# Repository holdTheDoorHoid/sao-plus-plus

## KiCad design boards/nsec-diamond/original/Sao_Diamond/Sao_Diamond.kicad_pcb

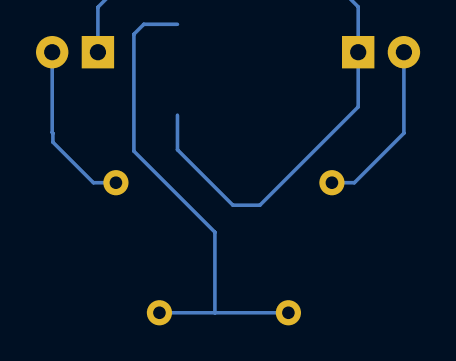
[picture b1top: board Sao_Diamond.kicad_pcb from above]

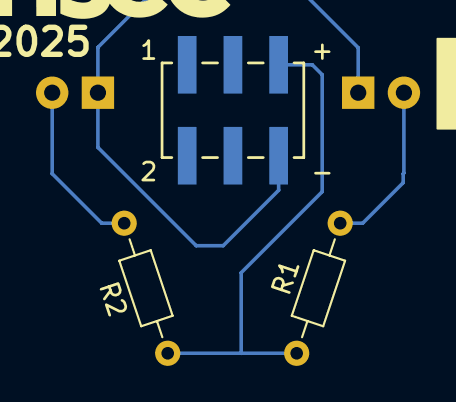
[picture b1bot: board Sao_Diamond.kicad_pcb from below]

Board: 2 copper layers, 5 parts (3 on the bottom side), 4 nets.

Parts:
D1, D2: LED; LED_D3.0mm
J1: SAO Connector SMD
R1, R2: 330; R_Axial_DIN0204_L3.6mm_D1.6mm_P7.62mm_Horizontal

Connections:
+3.3V: J1.5 (3V3), R1.1, R2.1
GND: D1.1 (K), D2.1 (K), J1.6 (GND)
unnamed: D1.2 (A), R1.2
unnamed: D2.2 (A), R2.2

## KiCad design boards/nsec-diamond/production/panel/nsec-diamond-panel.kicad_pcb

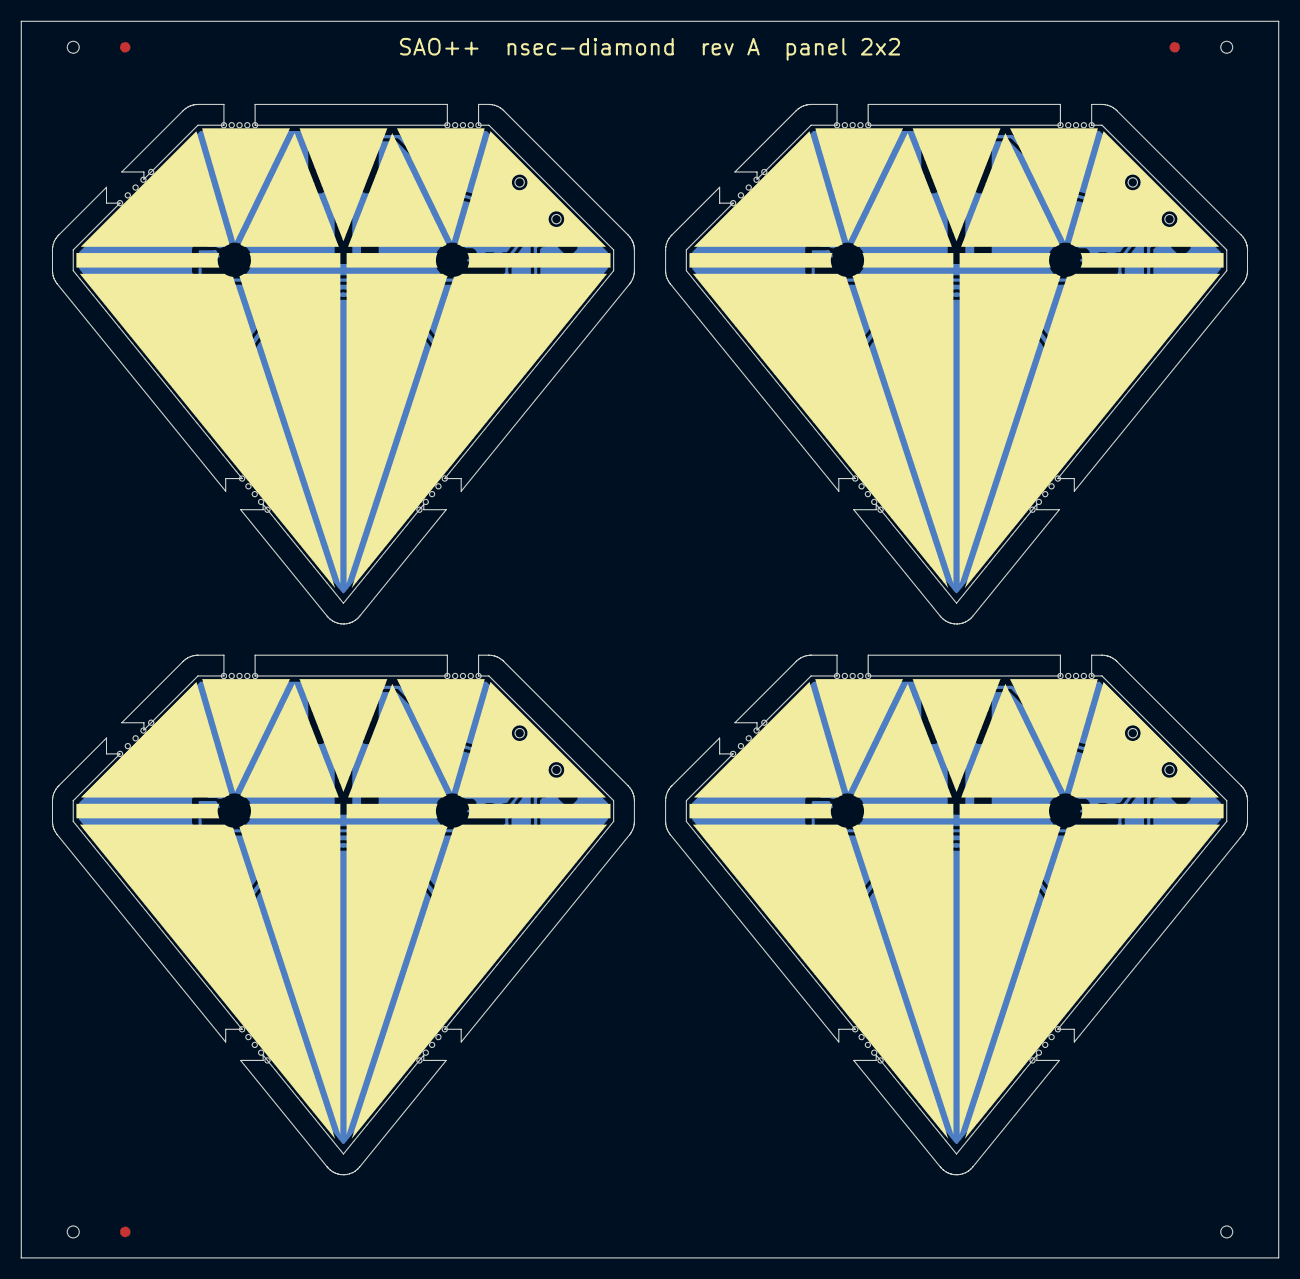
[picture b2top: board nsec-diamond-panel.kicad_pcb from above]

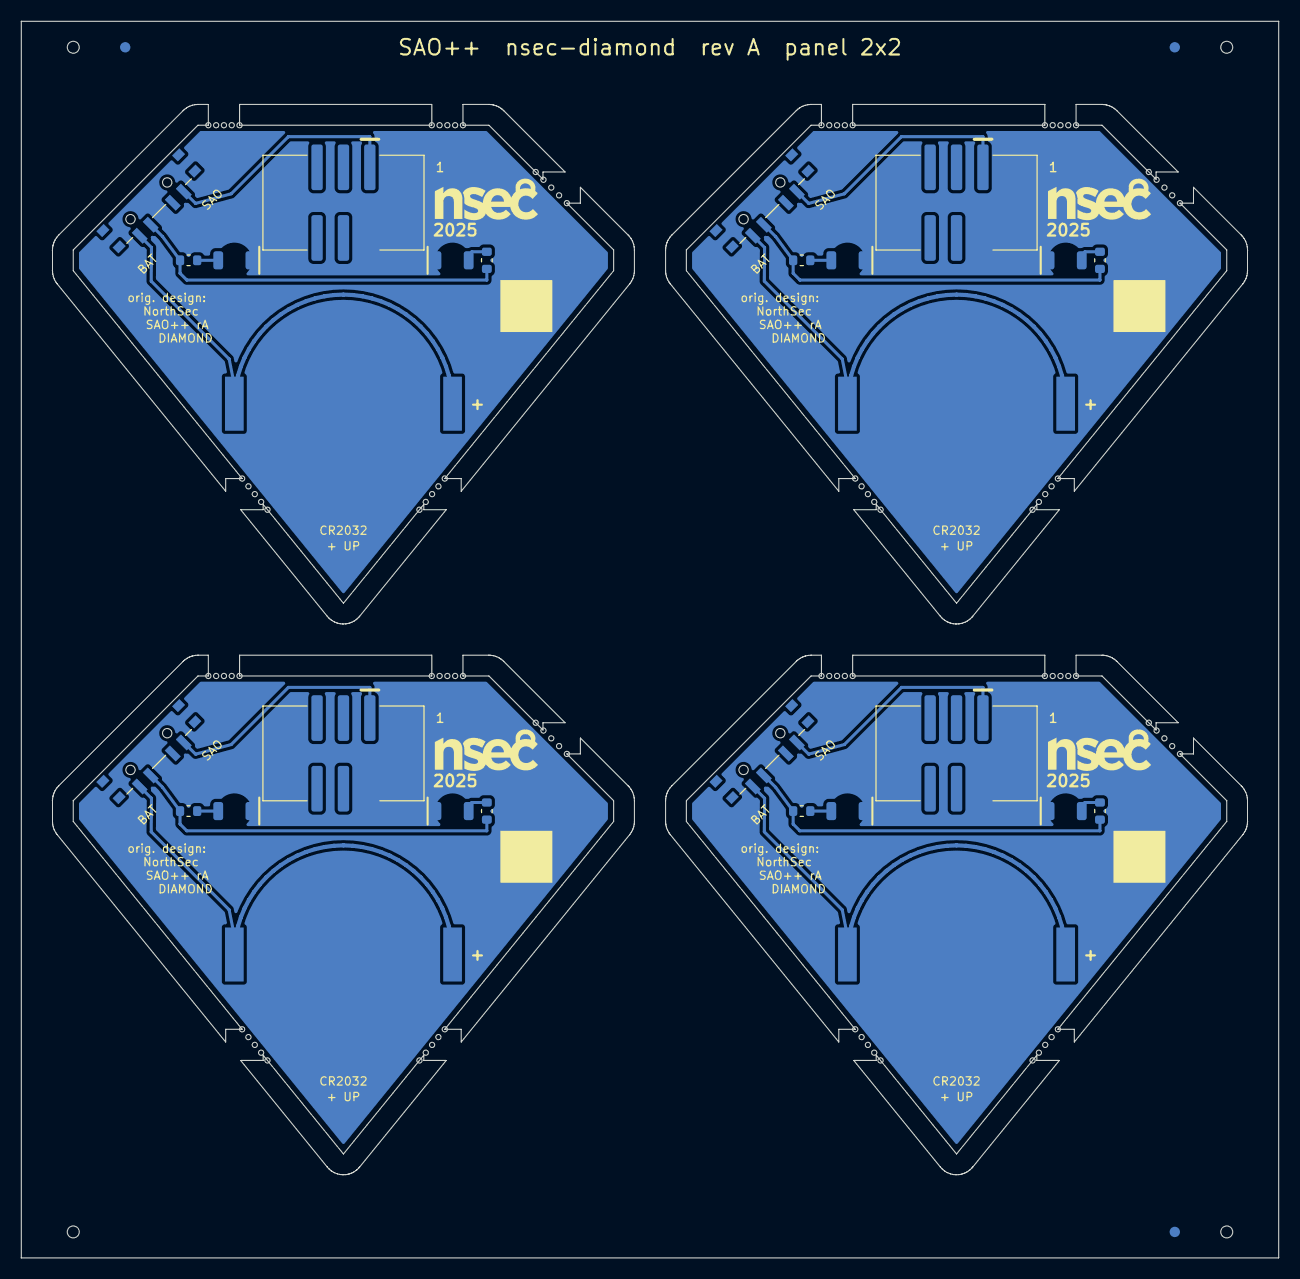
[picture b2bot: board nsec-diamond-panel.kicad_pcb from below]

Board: 2 copper layers, 121.0 x 119.0 mm, 28 parts (28 on the bottom side), 24 nets.

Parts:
BT101, BT201, BT301, BT401: CR2032; SAOPP_BAT-01_CR2032_SMD_TE_BAT-HLD-001
D101, D102, D201, D202, D301, D302, D401, D402: white; SAOPP_LED-10_1206_ReverseMount_ThroughBoard
J101, J201, J301, J401: SAO v1.69bis; SAOPP_CONN-01_BoxHeader_2x03_P2.54mm_SMD_XFCN_BH254VS-6P
R101, R102, R201, R202, R301, R302, R401, R402: 1.3k; SAOPP_R_0603_1608Metric
SW101, SW201, SW301, SW401: SAO / OFF / BAT; SAOPP_SW-01_Slide_SP3T_CK_PCM13SMTR

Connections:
B2-GND: BT201.2, D201.1, D202.1, J201.2
B2-LED1_A: D201.2, R201.2
B2-LED2_A: D202.2, R202.2
B2-VBAT: BT201.1, SW201.4
B2-VLOAD: R201.1, R202.1, SW201.3
B2-VSAO: J201.1, SW201.1
B3-GND: BT301.2, D301.1, D302.1, J301.2
B3-LED1_A: D301.2, R301.2
B3-LED2_A: D302.2, R302.2
B3-VBAT: BT301.1, SW301.4
B3-VLOAD: R301.1, R302.1, SW301.3
B3-VSAO: J301.1, SW301.1
B4-GND: BT401.2, D401.1, D402.1, J401.2
B4-LED1_A: D401.2, R401.2
B4-LED2_A: D402.2, R402.2
B4-VBAT: BT401.1, SW401.4
B4-VLOAD: R401.1, R402.1, SW401.3
B4-VSAO: J401.1, SW401.1
GND: BT101.2, D101.1, D102.1, J101.2
LED1_A: D101.2, R101.2
LED2_A: D102.2, R102.2
VBAT: BT101.1, SW101.4
VLOAD: R101.1, R102.1, SW101.3
VSAO: J101.1, SW101.1

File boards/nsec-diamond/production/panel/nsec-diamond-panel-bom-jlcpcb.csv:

Comment,Designator,Footprint,LCSC Part #
CR2032,"BT101,BT201,BT301,BT401",SAOPP_BAT-01_CR2032_SMD_TE_BAT-HLD-001,C7501066
white,"D101,D102,D201,D202,D301,D302,D401,D402",SAOPP_LED-10_1206_ReverseMount_ThroughBoard,C575513
SAO v1.69bis,"J101,J201,J301,J401",SAOPP_CONN-01_BoxHeader_2x03_P2.54mm_SMD_XFCN_BH254VS-6P,C492445
1.3k,"R101,R102,R201,R202,R301,R302,R401,R402",SAOPP_R_0603_1608Metric,C22767
SAO / OFF / BAT,"SW101,SW201,SW301,SW401",SAOPP_SW-01_Slide_SP3T_CK_PCM13SMTR,C221842

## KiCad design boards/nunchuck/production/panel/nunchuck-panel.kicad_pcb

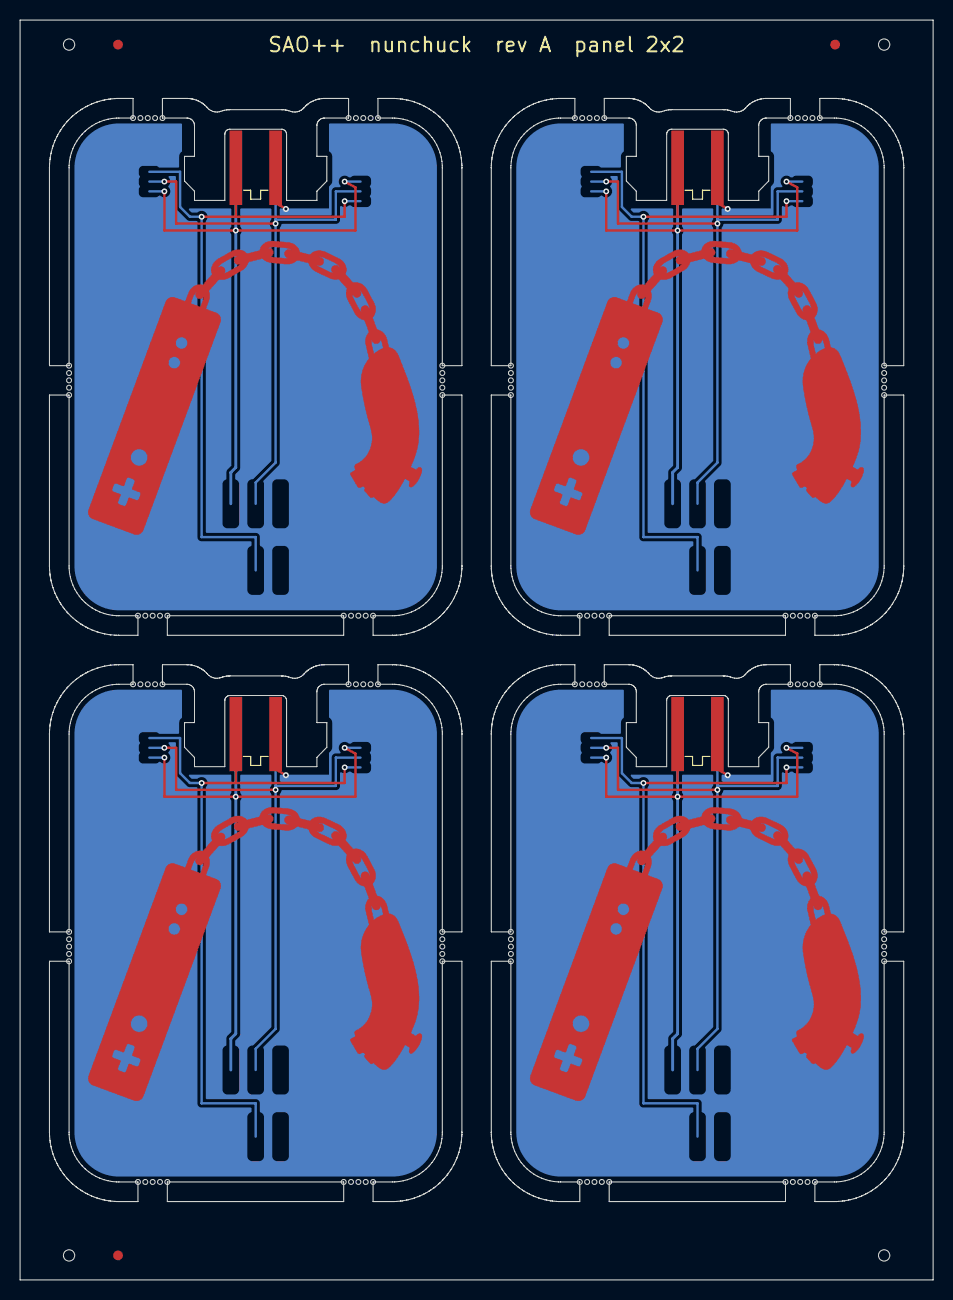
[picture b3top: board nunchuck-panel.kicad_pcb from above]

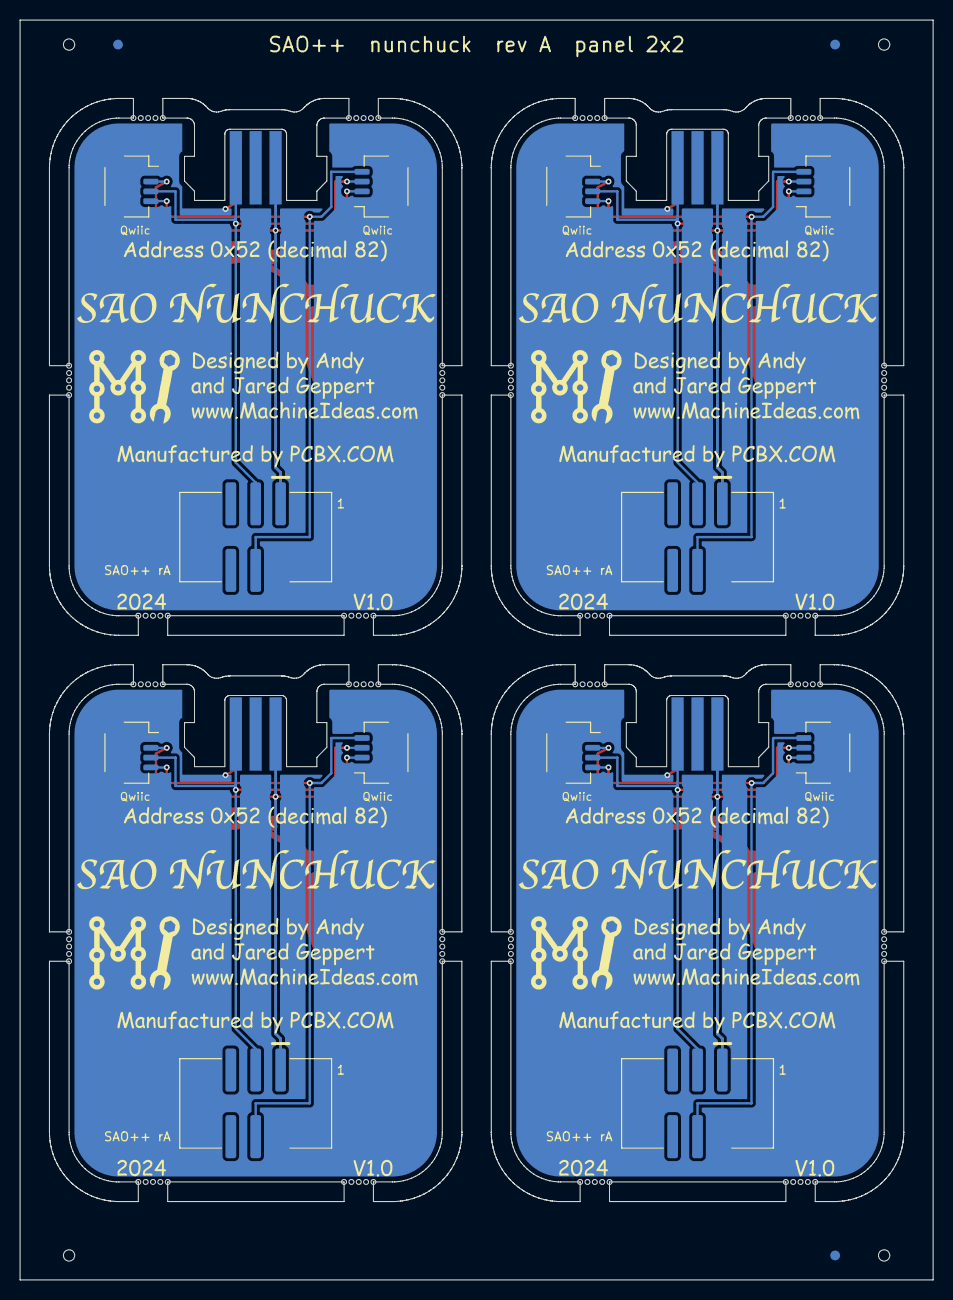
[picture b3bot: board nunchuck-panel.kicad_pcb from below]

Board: 2 copper layers, 93.2 x 128.6 mm, 20 parts (16 on the bottom side), 16 nets.

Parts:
J101, J201, J301, J401: SAO v1.69bis; SAOPP_CONN-01_BoxHeader_2x03_P2.54mm_SMD_XFCN_BH254VS-6P
J102, J202, J302, J402: Wii Nunchuk plug; Nunchuk-male
J103, J104, J203, J204, J303, J304, J403, J404: Qwiic; JST_SH_SM04B-SRSS-TB_1x04-1MP_P1.00mm_Horizontal
L1, L1#2, L1#3, L1#4: Machine_Ideas_logo

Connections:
3V3: J101.1, J102.3, J103.2, J104.2
B2-3V3: J201.1, J202.3, J203.2, J204.2
B2-GND: J201.2, J202.6, J203.1, J203.MP, J204.1, J204.MP
B2-SCL: J201.4, J202.4, J203.4, J204.4
B2-SDA: J201.3, J202.1, J203.3, J204.3
B3-3V3: J301.1, J302.3, J303.2, J304.2
B3-GND: J301.2, J302.6, J303.1, J303.MP, J304.1, J304.MP
B3-SCL: J301.4, J302.4, J303.4, J304.4
B3-SDA: J301.3, J302.1, J303.3, J304.3
B4-3V3: J401.1, J402.3, J403.2, J404.2
B4-GND: J401.2, J402.6, J403.1, J403.MP, J404.1, J404.MP
B4-SCL: J401.4, J402.4, J403.4, J404.4
B4-SDA: J401.3, J402.1, J403.3, J404.3
GND: J101.2, J102.6, J103.1, J103.MP, J104.1, J104.MP
SCL: J101.4, J102.4, J103.4, J104.4
SDA: J101.3, J102.1, J103.3, J104.3

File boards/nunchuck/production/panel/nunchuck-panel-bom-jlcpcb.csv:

Comment,Designator,Footprint,LCSC Part #
SAO v1.69bis,"J101,J201,J301,J401",SAOPP_CONN-01_BoxHeader_2x03_P2.54mm_SMD_XFCN_BH254VS-6P,C492445
Qwiic,"J103,J104,J203,J204,J303,J304,J403,J404",JST_SH_SM04B-SRSS-TB_1x04-1MP_P1.00mm_Horizontal,C160404
